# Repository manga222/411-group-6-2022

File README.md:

# ECE 425 Disco Light Tower

Author: Manuel Garcia, Mercedes Newton, Willenton Bridges, Alice Ma

## Introduction

A light display tower that utilized audio input to create a unique and exciting light show. The tower will change light color and intensity according to the music in order to always create the perfect vibe. This is the perfect product for all ages, specifically anyone who enjoys music and excellent vibes. This is a practical and fun product that we could all see having in our homes.

### Motivation

Searching for a light centerpiece, we identified needs that we had not seen satiated in the current market
Our prototype provides a solution that is…..
* Affordable 
* Portable
* Compatible with any audio
* Unique 
* aesthetically pleasing

## Proposed Design Requirements

* Must change LED color according to surrounding sound and/or music
* Must be aesthetically pleasing
* Must be safe
* Must be user friendly (single power button)
* Must be portable
* Should change LED intensity / frequency according to surrounding sound and/or music
* Should be less than 30lbs
* Should be 2 feet tall
* Should have a metal base
* Should have a disco ball and RGB spotlight
* Should have soft bottom to prevent scratching floor
* May input music internally through microcontroller and use FFT to filter frequency
* May be battery powered
* May have light intensity settings
* May have amplifying speakers

### Physical Design

* Helix shape for optimal height, light, and appearance
* Lights attached on interior of steel bars to prevent harshness
* 6 bars to both allow for a multitude of light strips yet stay lightweight and mobile
* Circuitry placed in base and out of sight
* Disco ball centered and hung at the top of tower

### System Architecture

* ESP-32

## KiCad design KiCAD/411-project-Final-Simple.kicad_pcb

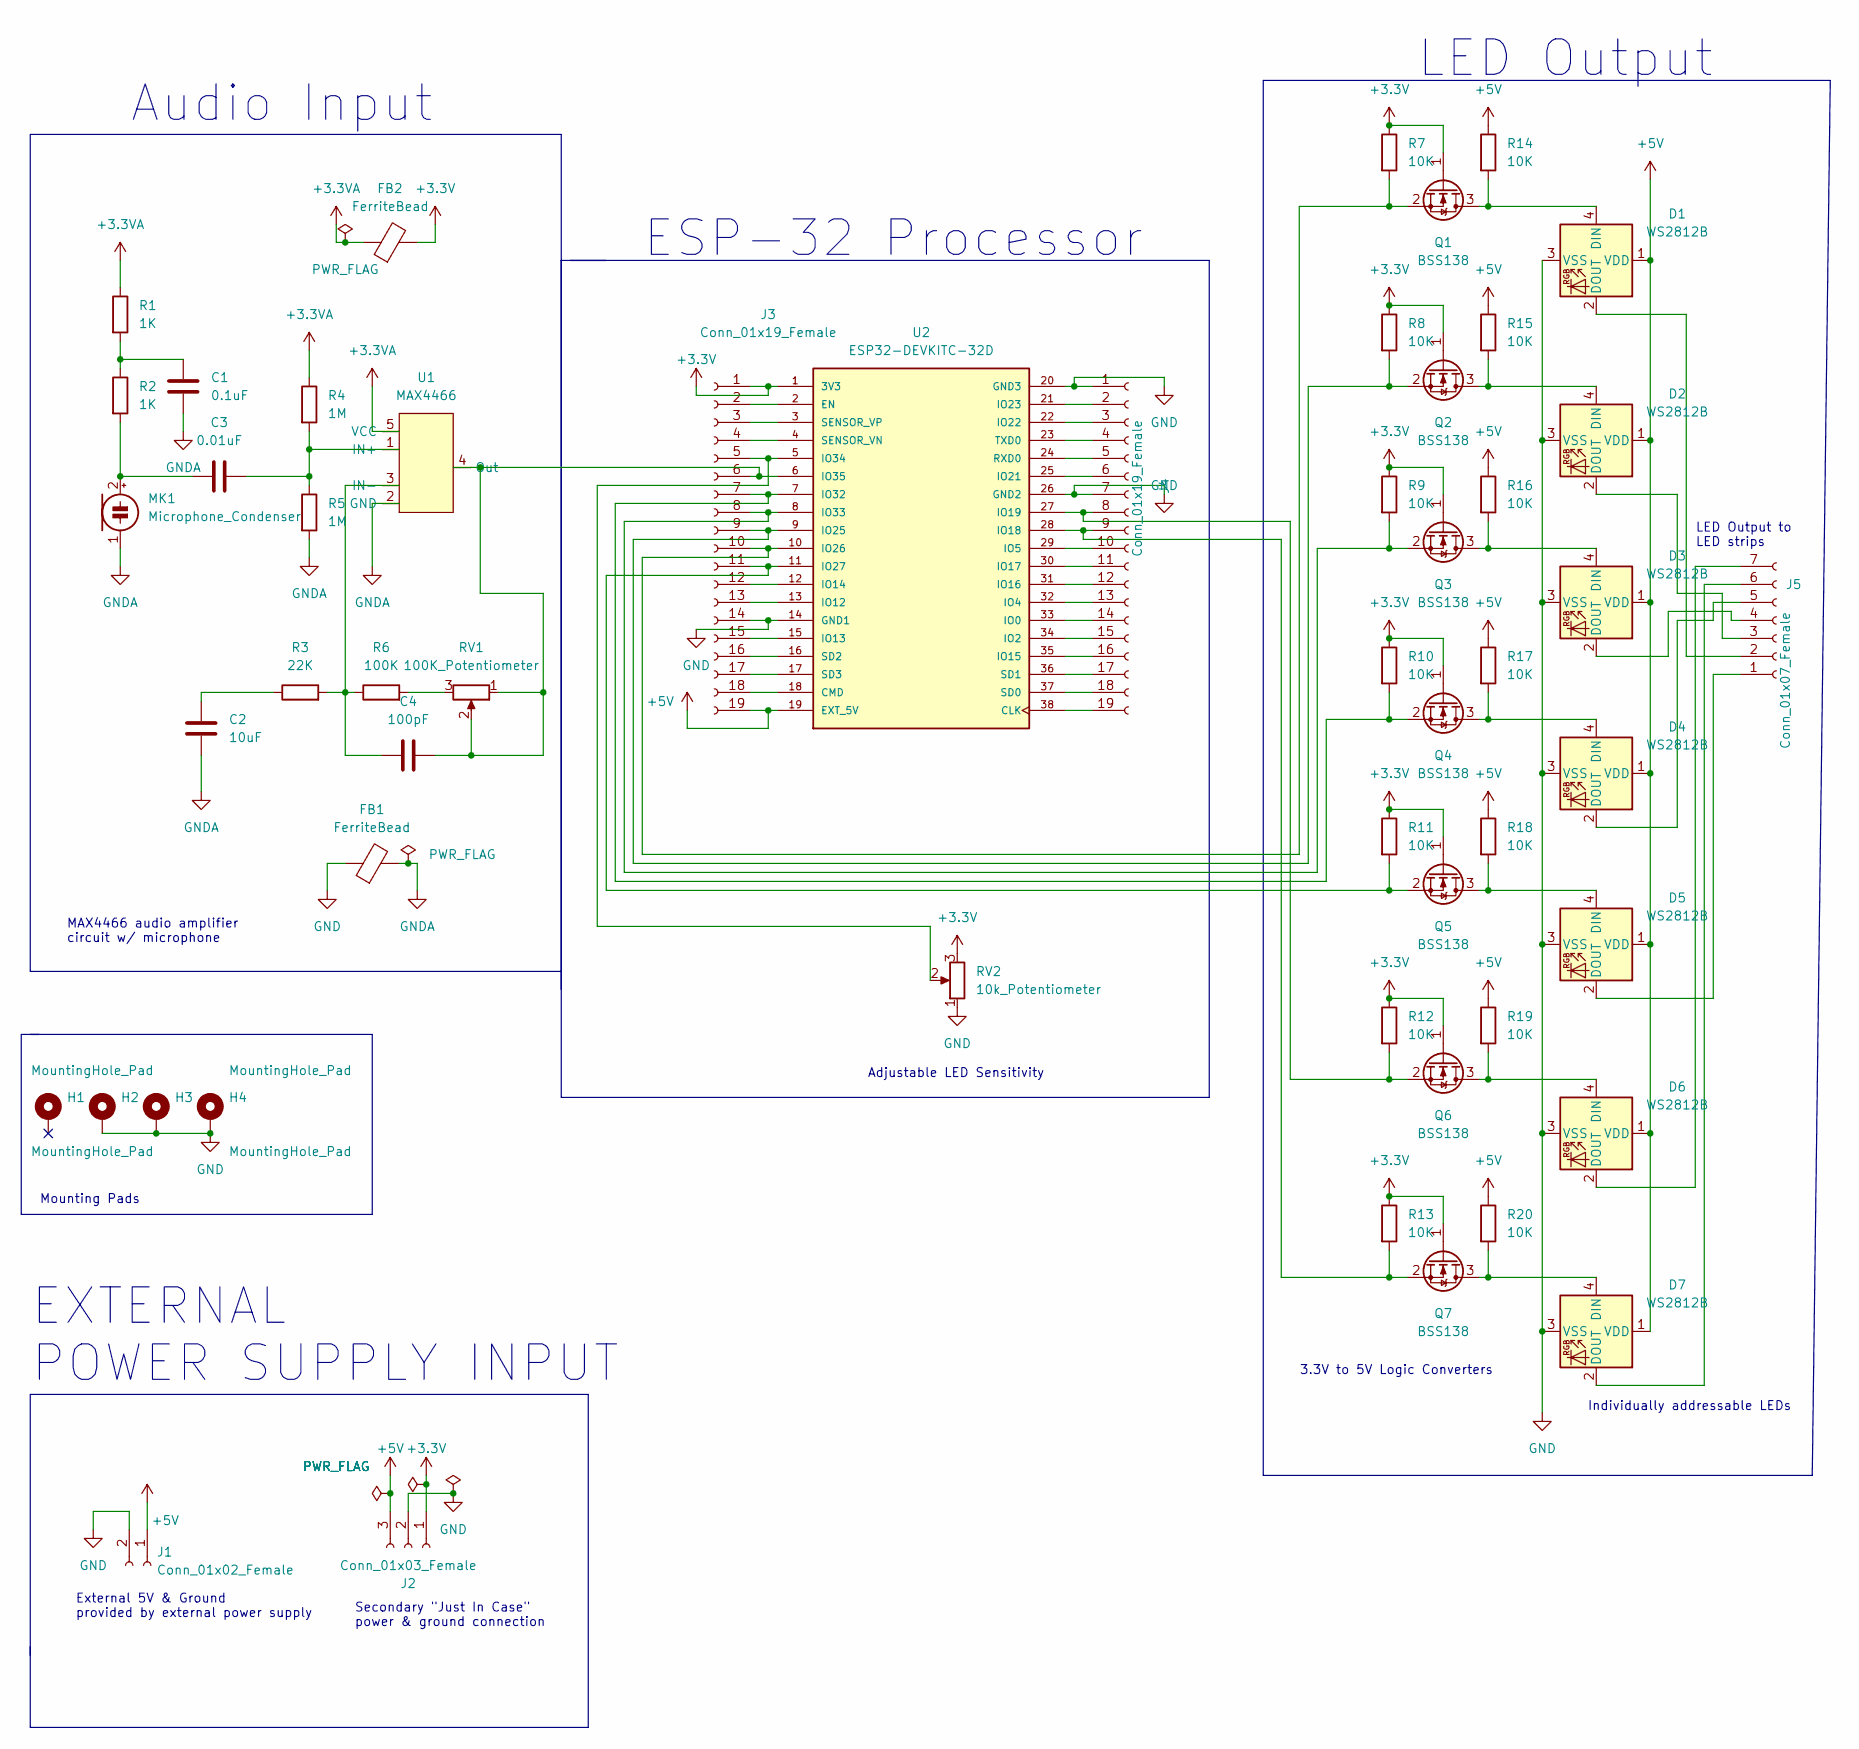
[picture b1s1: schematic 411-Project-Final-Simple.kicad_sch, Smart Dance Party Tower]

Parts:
C1: 0.1uF; C_0603_1608Metric
C2: 10uF; C_0805_2012Metric
C3: 0.01uF; C_0603_1608Metric
C4: 100pF; C_0603_1608Metric
D1, D2, D3, D4, D5, D6, D7: WS2812B; LED_WS2812B_PLCC4_5.0x5.0mm_P3.2mm
FB1, FB2: FerriteBead; L_0603_1608Metric
H1, H2, H3, H4: MountingHole_Pad; MountingHole_2.2mm_M2_Pad
J1: Conn_01x02_Female; PinSocket_1x02_P2.54mm_Vertical
J2: Conn_01x03_Female; PinSocket_1x03_P2.54mm_Vertical
J3, J4: Conn_01x19_Female; PinSocket_1x19_P2.54mm_Vertical
J5: Conn_01x07_Female; PinSocket_1x07_P2.54mm_Vertical
MK1: Microphone_Condenser; MIC_CMA-4544PF-W
Q1, Q2, Q3, Q4, Q5, Q6, Q7: BSS138; SOT-23
R1, R2: 1K; R_0805_2012Metric
R3: 22K; R_0603_1608Metric
R4, R5: 1M; R_1210_3225Metric
R6: 100K; R_0805_2012Metric
R7, R8, R9, R10, R11, R12, R13, R14, R15, R16, R17, R18, R19, R20: 10K; R_0805_2012Metric
RV1: 100K_Potentiometer; PTA4543-2015DPA103
RV2: 10k_Potentiometer; PTA4543-2015DPA103
U1: MAX4466; MAX4466EXK&plus_T
U2: ESP32-DEVKITC-32D; MODULE_ESP32-DEVKITC-32D; PARTREV 4

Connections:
+3.3V: FB2.2, J2.1, J3.1, Q1.1 (G), Q2.1 (G), Q3.1 (G), Q4.1 (G), Q5.1 (G), Q6.1 (G), Q7.1 (G), R7.1, R8.1, R9.1, R10.1, R11.1, R12.1, R13.1, RV2.3, U2.1 (3V3); also elsewhere on the board
+3.3VA: FB2.1, R1.1, R4.1, U1.5 (VCC)
+5V: D1.1 (VDD), D2.1 (VDD), D3.1 (VDD), D4.1 (VDD), D5.1 (VDD), D6.1 (VDD), D7.1 (VDD), J1.1, J2.3, J3.19, R14.1, R15.1, R16.1, R17.1, R18.1, R19.1, R20.1, U2.19 (EXT_5V); also elsewhere on the board
GND: D1.3 (VSS), D2.3 (VSS), D3.3 (VSS), D4.3 (VSS), D5.3 (VSS), D6.3 (VSS), D7.3 (VSS), FB1.1, H2.1, H3.1, H4.1, J1.2, J2.2, J3.14, J4.1, J4.7, RV2.1, U2.14 (GND1), U2.20 (GND3), U2.26 (GND2); also elsewhere on the board
GNDA: C1.2, C2.1, FB1.2, MK1.1 (-), R5.2, U1.2 (GND)
unnamed: C1.1, R1.2, R2.1
unnamed: C2.2, R3.1
unnamed: C3.1, MK1.2 (+), R2.2
unnamed: C3.2, R4.2, R5.1, U1.1 (IN+)
unnamed: C4.1, R3.2, R6.1, U1.3 (IN-)
unnamed 10: C4.2, J3.6, RV1.1, RV1.2, U1.4 (Out), U2.6 (IO35); also elsewhere on the board
unnamed 11: J3.2, U2.2 (EN); also elsewhere on the board
unnamed 12: J3.3, U2.3 (SENSOR_VP); also elsewhere on the board
unnamed 13: J3.4, U2.4 (SENSOR_VN); also elsewhere on the board
unnamed 14: J3.5, RV2.2, U2.5 (IO34); also elsewhere on the board
unnamed 15: J3.7, Q4.2 (S), R10.2, U2.7 (IO32); also elsewhere on the board
unnamed 16: J3.8, Q3.2 (S), R9.2, U2.8 (IO33); also elsewhere on the board
unnamed 17: J3.9, Q2.2 (S), R8.2, U2.9 (IO25); also elsewhere on the board
unnamed 18: J3.10, Q1.2 (S), R7.2, U2.10 (IO26); also elsewhere on the board
unnamed 19: J3.11, Q5.2 (S), R11.2, U2.11 (IO27); also elsewhere on the board
unnamed 20: J3.12, U2.12 (IO14); also elsewhere on the board
unnamed 21: J3.13, U2.13 (IO12); also elsewhere on the board
unnamed 22: J3.15, U2.15 (IO13); also elsewhere on the board
unnamed 23: J3.16, U2.16 (SD2); also elsewhere on the board
unnamed 24: J3.17, U2.17 (SD3); also elsewhere on the board
unnamed 25: J3.18, U2.18 (CMD); also elsewhere on the board
unnamed 26: J4.2, U2.21 (IO23); also elsewhere on the board
unnamed 27: J4.3, U2.22 (IO22); also elsewhere on the board
unnamed 28: J4.4, U2.23 (TXD0); also elsewhere on the board
unnamed 29: J4.5, U2.24 (RXD0); also elsewhere on the board
unnamed 30: J4.6, U2.25 (IO21); also elsewhere on the board
unnamed 31: J4.8, Q6.2 (S), R12.2, U2.27 (IO19); also elsewhere on the board
unnamed 32: J4.9, Q7.2 (S), R13.2, U2.28 (IO18); also elsewhere on the board
unnamed 33: J4.10, U2.29 (IO5); also elsewhere on the board
unnamed 34: J4.11, U2.30 (IO17); also elsewhere on the board
unnamed 35: J4.12, U2.31 (IO16); also elsewhere on the board
unnamed 36: J4.13, U2.32 (IO4); also elsewhere on the board
unnamed 37: J4.14, U2.33 (IO0); also elsewhere on the board
unnamed 38: J4.15, U2.34 (IO2); also elsewhere on the board
unnamed 39: J4.16, U2.35 (IO15); also elsewhere on the board
unnamed 40: J4.17, U2.36 (SD1); also elsewhere on the board
unnamed 41: J4.18, U2.37 (SD0); also elsewhere on the board
unnamed 42: J4.19, U2.38 (CLK); also elsewhere on the board
unnamed 43: D5.2 (DOUT), J5.1; also elsewhere on the board
unnamed 44: D1.2 (DOUT), J5.2; also elsewhere on the board
unnamed 45: D2.2 (DOUT), J5.3; also elsewhere on the board
unnamed 46: D3.2 (DOUT), J5.4; also elsewhere on the board
unnamed 47: D4.2 (DOUT), J5.5; also elsewhere on the board
unnamed 48: D7.2 (DOUT), J5.6; also elsewhere on the board
unnamed 49: D6.2 (DOUT), J5.7; also elsewhere on the board
unnamed: D1.4 (DIN), Q1.3 (D), R14.2
unnamed: D2.4 (DIN), Q2.3 (D), R15.2
unnamed: D3.4 (DIN), Q3.3 (D), R16.2
unnamed: D4.4 (DIN), Q4.3 (D), R17.2
unnamed: D5.4 (DIN), Q5.3 (D), R18.2
unnamed: D6.4 (DIN), Q6.3 (D), R19.2
unnamed: D7.4 (DIN), Q7.3 (D), R20.2
unnamed: R6.2, RV1.3

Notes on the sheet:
EXTERNAL POWER SUPPLY INPUT
MAX4466 audio amplifier circuit w/ microphone
External 5V & Ground provided by external power supply
LED Output
ESP-32 Processor
Individually addressable LEDs
Adjustable LED Sensitivity
Audio Input
3.3V to 5V Logic Converters
Mounting Pads
Secondary "Just In Case" power & ground connection
LED Output to LED strips

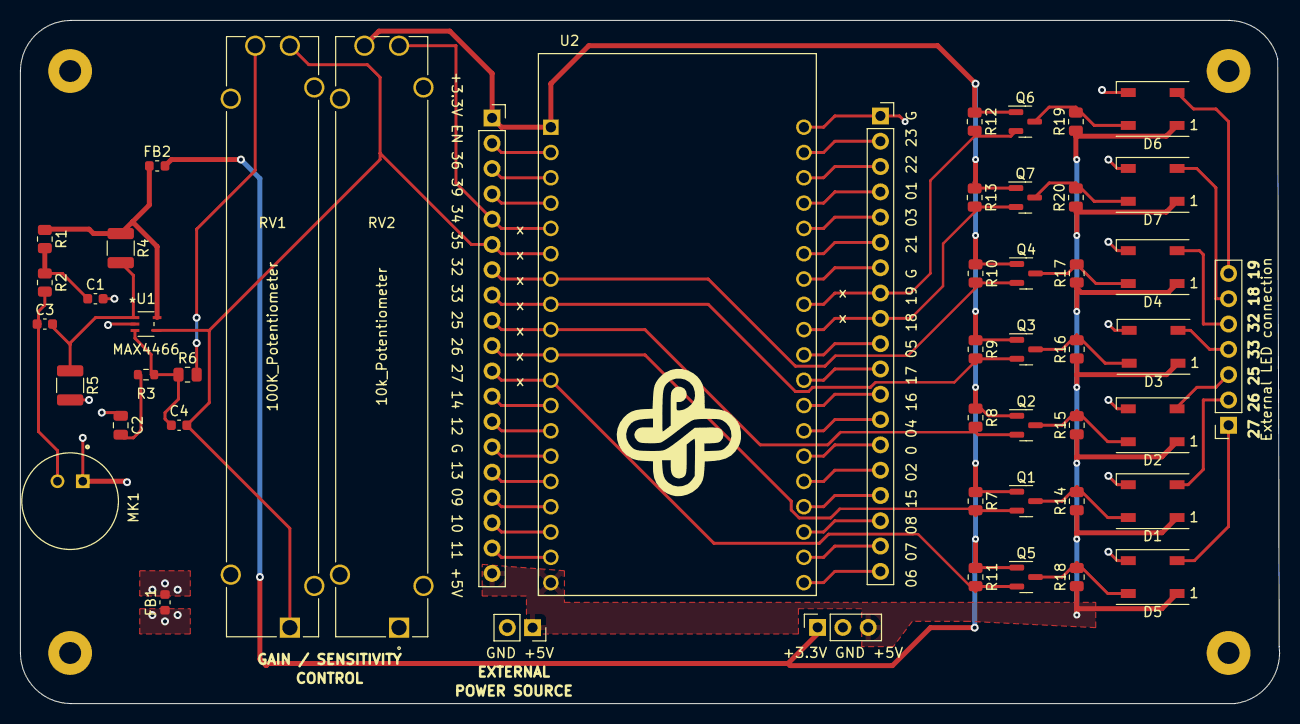
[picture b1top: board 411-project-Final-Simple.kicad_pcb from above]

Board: 2 copper layers, 126.4 x 68.6 mm, 54 parts (0 on the bottom side), 58 nets.

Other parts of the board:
06 07 08 15 02 0 04 16 17 05 18 19 G  21 03 01 22 23 G: Conn_01x19_Female; PinSocket_1x19_P2.54mm_Vertical
+3.3V EN 36 39 34 35 32 33 25 26 27 14 12 G 13 09 10 11 +5V: Conn_01x19_Female; PinSocket_1x19_P2.54mm_Vertical
+3.3V GND +5V: Conn_01x03_Female; PinSocket_1x03_P2.54mm_Vertical
External LED connection: Conn_01x07_Female; PinSocket_1x07_P2.54mm_Vertical
GND +5V: Conn_01x02_Female; PinSocket_1x02_P2.54mm_Vertical

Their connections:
+3.3V: +3.3V EN 36 39 34 35 32 33 25 26 27 14 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.1, +3.3V GND +5V.1; also elsewhere on the board
+5V: +3.3V EN 36 39 34 35 32 33 25 26 27 14 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.19, +3.3V GND +5V.3, GND +5V.1; also elsewhere on the board
GND: 06 07 08 15 02 0 04 16 17 05 18 19 G 21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.1, 06 07 08 15 02 0 04 16 17 05 18 19 G 21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.7, +3.3V EN 36 39 34 35 32 33 25 26 27 14 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.14, +3.3V GND +5V.2, GND +5V.2; also elsewhere on the board
unnamed 10: +3.3V EN 36 39 34 35 32 33 25 26 27 14 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.6; also elsewhere on the board
unnamed 11: +3.3V EN 36 39 34 35 32 33 25 26 27 14 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.2; also elsewhere on the board
unnamed 12: +3.3V EN 36 39 34 35 32 33 25 26 27 14 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.3; also elsewhere on the board
unnamed 13: +3.3V EN 36 39 34 35 32 33 25 26 27 14 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.4; also elsewhere on the board
unnamed 14: +3.3V EN 36 39 34 35 32 33 25 26 27 14 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.5; also elsewhere on the board
unnamed 15: +3.3V EN 36 39 34 35 32 33 25 26 27 14 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.7; also elsewhere on the board
unnamed 16: +3.3V EN 36 39 34 35 32 33 25 26 27 14 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.8; also elsewhere on the board
unnamed 17: +3.3V EN 36 39 34 35 32 33 25 26 27 14 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.9; also elsewhere on the board
unnamed 18: +3.3V EN 36 39 34 35 32 33 25 26 27 14 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.10; also elsewhere on the board
unnamed 19: +3.3V EN 36 39 34 35 32 33 25 26 27 14 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.11; also elsewhere on the board
unnamed 20: +3.3V EN 36 39 34 35 32 33 25 26 27 14 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.12; also elsewhere on the board
unnamed 21: +3.3V EN 36 39 34 35 32 33 25 26 27 14 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.13; also elsewhere on the board
unnamed 22: +3.3V EN 36 39 34 35 32 33 25 26 27 14 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.15; also elsewhere on the board
unnamed 23: +3.3V EN 36 39 34 35 32 33 25 26 27 14 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.16; also elsewhere on the board
unnamed 24: +3.3V EN 36 39 34 35 32 33 25 26 27 14 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.17; also elsewhere on the board
unnamed 25: +3.3V EN 36 39 34 35 32 33 25 26 27 14 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.18; also elsewhere on the board
unnamed 26: 06 07 08 15 02 0 04 16 17 05 18 19 G 21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.2; also elsewhere on the board
unnamed 27: 06 07 08 15 02 0 04 16 17 05 18 19 G 21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.3; also elsewhere on the board
unnamed 28: 06 07 08 15 02 0 04 16 17 05 18 19 G 21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.4; also elsewhere on the board
unnamed 29: 06 07 08 15 02 0 04 16 17 05 18 19 G 21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.5; also elsewhere on the board
unnamed 30: 06 07 08 15 02 0 04 16 17 05 18 19 G 21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.6; also elsewhere on the board
unnamed 31: 06 07 08 15 02 0 04 16 17 05 18 19 G 21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.8; also elsewhere on the board
unnamed 32: 06 07 08 15 02 0 04 16 17 05 18 19 G 21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.9; also elsewhere on the board
unnamed 33: 06 07 08 15 02 0 04 16 17 05 18 19 G 21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.10; also elsewhere on the board
unnamed 34: 06 07 08 15 02 0 04 16 17 05 18 19 G 21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.11; also elsewhere on the board
unnamed 35: 06 07 08 15 02 0 04 16 17 05 18 19 G 21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.12; also elsewhere on the board
unnamed 36: 06 07 08 15 02 0 04 16 17 05 18 19 G 21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.13; also elsewhere on the board
unnamed 37: 06 07 08 15 02 0 04 16 17 05 18 19 G 21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.14; also elsewhere on the board
unnamed 38: 06 07 08 15 02 0 04 16 17 05 18 19 G 21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.15; also elsewhere on the board
unnamed 39: 06 07 08 15 02 0 04 16 17 05 18 19 G 21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.16; also elsewhere on the board
unnamed 40: 06 07 08 15 02 0 04 16 17 05 18 19 G 21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.17; also elsewhere on the board
unnamed 41: 06 07 08 15 02 0 04 16 17 05 18 19 G 21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.18; also elsewhere on the board
unnamed 42: 06 07 08 15 02 0 04 16 17 05 18 19 G 21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.19; also elsewhere on the board
unnamed 43: External LED connection.1; also elsewhere on the board
unnamed 44: External LED connection.2; also elsewhere on the board
unnamed 45: External LED connection.3; also elsewhere on the board
unnamed 46: External LED connection.4; also elsewhere on the board
unnamed 47: External LED connection.5; also elsewhere on the board
unnamed 48: External LED connection.6; also elsewhere on the board
unnamed 49: External LED connection.7; also elsewhere on the board

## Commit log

2022-11-06 Breadboard Prototype
2022-12-08 Finished light tower
2022-12-08 Finished LED tower
2022-12-08 Prototype code
    This code communicated only for a single LED strip and single core for the ESP-32.
2022-12-08 Final code version
2022-12-08 Functional Design Decomposition
2022-12-08 Video of MVP
2022-12-08 KiCAD files
2022-12-09 folder/file
2022-12-09 Project Ideas & Descriptions
2022-12-09 Product Design Specification
2022-12-09 Project Schedule
2022-12-09 Bill of Materials
2022-12-09 Preliminary Schematic
2022-12-09 Updated Schematic Prelim Layout
2022-12-09 Rough Draft Layout/ Schematic
2022-12-09 Final CAD Design
2022-12-09 Test Plans

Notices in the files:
parts and their libraries:
Copyright 2021 Accelerated Designs. All rights reserved.
